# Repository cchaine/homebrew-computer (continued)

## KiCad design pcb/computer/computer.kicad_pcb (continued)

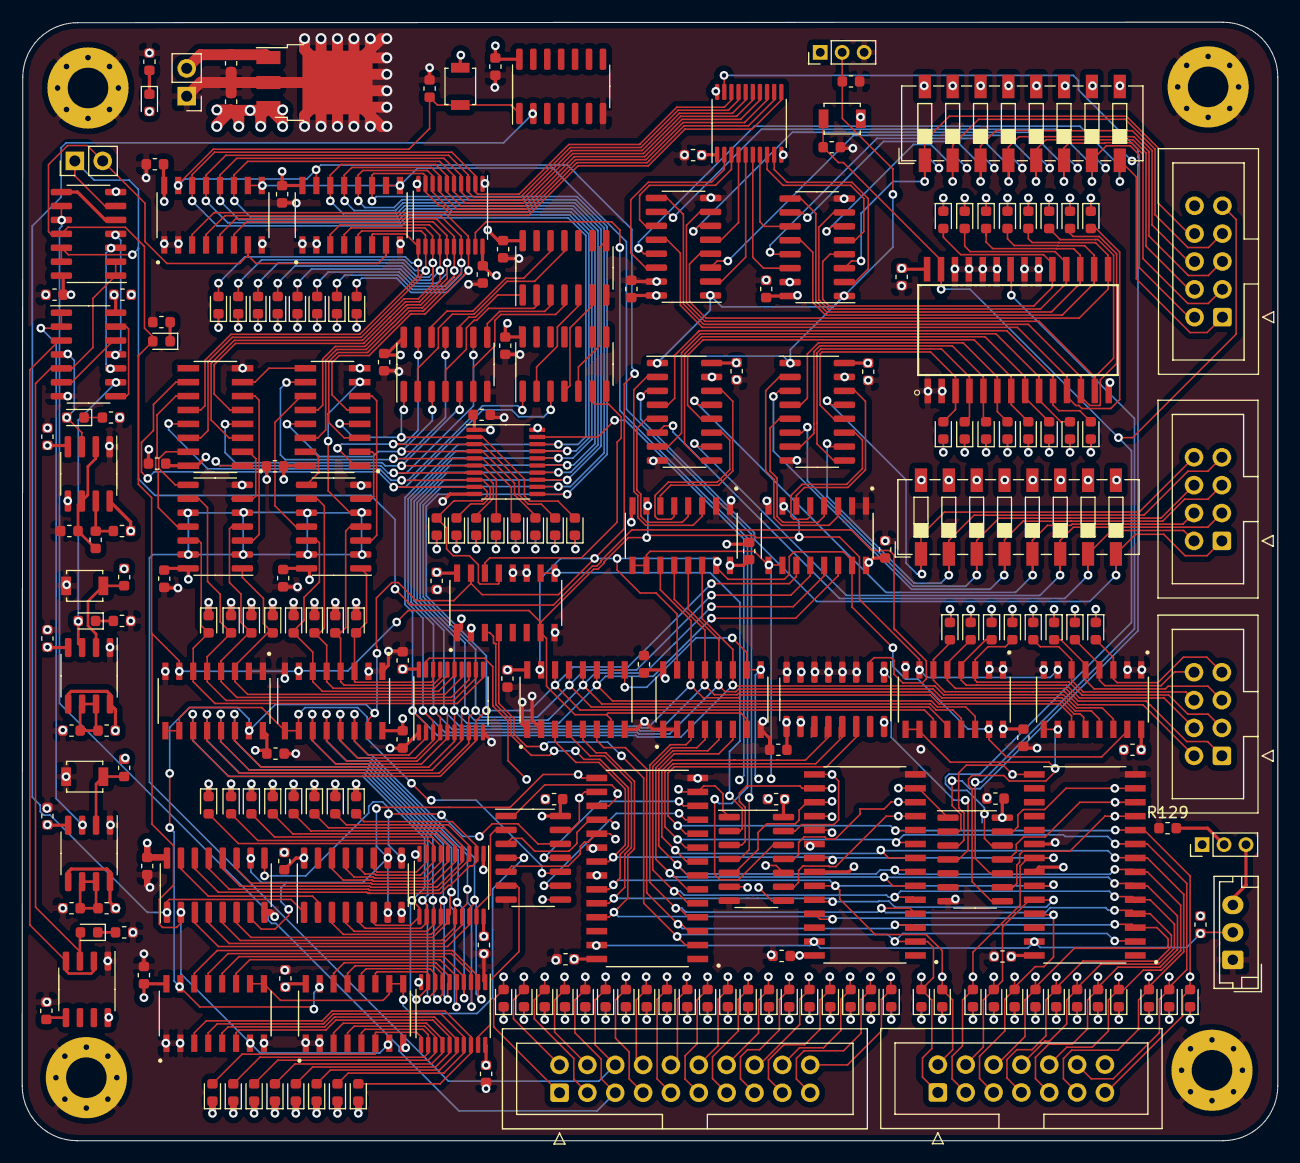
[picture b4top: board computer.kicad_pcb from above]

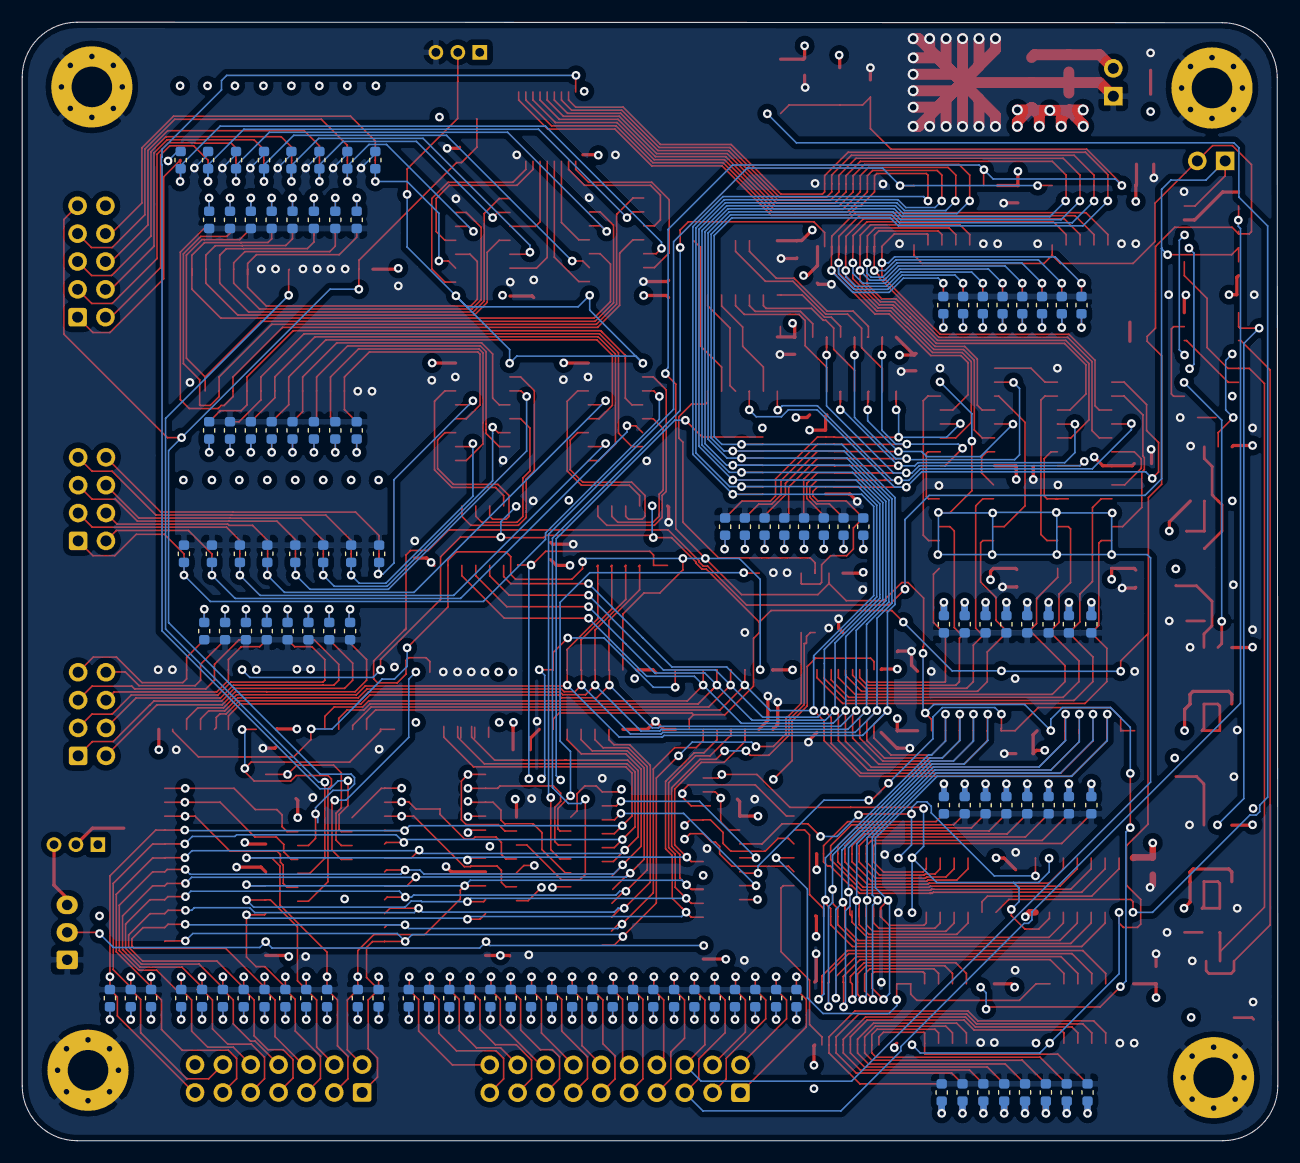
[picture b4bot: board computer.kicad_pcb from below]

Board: 4 copper layers, 114.5 x 102.0 mm, 351 parts (113 on the bottom side), 304 nets.

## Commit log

2020-04-22 Add the instruction set document
2020-04-23 Fix instruction opcode
2020-04-26 Remove mov for pc and sp
2020-04-27 Add ldr and str from sp
2020-08-19 Add rev1 pcb
2020-09-07 Update on the pcb
2020-09-12 Update pcb2
2020-09-13 Finished pcb2
2020-10-17 Add new pcb
2020-10-18 Add the not instruction
2020-10-18 Add the schematic for the ALU and registers
2020-10-18 Add part of the control logic
2020-10-21 Add clock generation
2020-10-21 Add resistor nets for bus termination
2020-10-22 Add the memory interface logic
2020-10-23 Add beginning of peripheral ios
2020-10-23 Keep working on the peripheral interface
2020-10-24 Remove the address bus as it would require too big of a connector
2020-10-24 Remove unnecessary address bus and unified the IO interface
2020-10-26 Add program counter
2020-11-01 Change the control logic CPLD for a bigger one
2020-11-01 Connect signals between modules
2020-11-01 Start changing global labels with local labels
2020-11-02 Start working on the pcb layout
2020-11-03 Keep working on the layout
2020-11-03 Add the board outline
2020-11-05 Finished working on the layout
2020-11-05 Add via stiching
2020-11-05 Add silkscreen
2020-11-05 Invert silkscreen on bottom
2020-11-06 Change connector for a more common one, and change the diode footprint
2020-11-09 Rev A complete
2020-11-10 Clean the repository structure
2020-11-10 Add gitignore
2020-11-22 Version 1.0
2020-11-22 Add computer-board v1.0 schematics
2020-11-24 Remove and change connectors for a mezzanine one
2020-11-24 Revision 2 is ready
    Need to wait for the testing of rev 1 before ordering
2021-01-05 added the compute board firmware module
2021-01-06 Removed submodule
2021-01-06 added firmware modules for the compute-board
2021-01-15 added pulldowns on diode logic
2021-03-02 startover
2021-03-04 add the register module pcb
2021-03-04 changed the mask clearance for plotting
2021-04-12 remove unneeded
2021-04-12 add the hdl project structure
2021-04-12 remove some comments
2021-04-12 add the program_counter file
2021-04-13 add a design of a counter
2021-04-13 change the header comments
2021-04-14 change the bus name in counter
2021-04-14 add the alu design
2021-04-14 remove the three state on the counter
2021-04-15 only add test files to the sim view
2021-04-15 add the register bank
2021-04-15 start adding the datapath
2021-04-16 add the beginning of the control logic
2021-04-19 add more instructions
2021-04-23 add usb to jtag interface
2021-04-24 add buffer to jtag interface
2021-04-27 add power supply
2021-04-28 add the usb to spi interface
2021-04-28 add both usb to jtag and usb to spi interface
2021-04-29 start adding processor fpga
2021-04-30 add flash memory
2021-05-02 add the din connector
2021-05-02 start associating footprints
2021-05-04 add tps541620 footprint
2021-05-10 add the front led glue logic
2021-05-10 add the led blinking logic
2021-05-10 add footprint for the button
2021-05-10 add components to pcb
2021-05-10 add 3d files to some footprints
2021-05-12 add every 3d models
2021-05-12 start placing components
2021-05-13 place components relative to each others
2021-05-13 keep working on the pcb
2021-05-15 add traces for the power supply
2021-06-25 change to lx9 and reduce power
2021-06-27 add sram
2021-07-04 route pol
2021-07-04 add decoupling caps
2021-07-04 place all components
2021-07-07 start the routing
2021-07-07 route decaps
2021-07-07 move components around
2021-07-07 rearanged component placement
2021-07-08 added silkscreen values
2021-07-08 route the sram
2021-07-11 keep routing the flash
2021-07-11 edit the connector pinout
2021-07-12 route the peripheral bus
2021-07-13 continue routing
2021-07-13 start adding power vias
